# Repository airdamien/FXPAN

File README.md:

# FXPAN

Two Nikon D800 bodies behind one Nikkor-W 180 mm f/5.6. A 50 × 75 mm
beamsplitter sends each body half of the field. The stitch is

**64.80 × 23.9 mm · 2.711:1 · 13248 × 4912 · 65.1 MP**

XPan is 65 × 24 mm at 2.708:1. It is shot from f/5.6 to f/22. The
Nikkor-W covers the stitch wide open. The 44 mm mouths fully clear the
extreme corners from f/8.4; at f/5.6 those corners still pass most of the
light, and the long axis stays clean. The iPhone is the viewfinder and the
stitcher, and it can release both bodies over USB. A Pi Zero and the trigger
board are optional. They pulse both 10-pin remotes together. A yoke is the
alternate base: the same triangle and the same screws, extended out to a
grip past R and a grip on the far side of the plate. The right grip has a
trigger on its front edge.

Buy list, print list, and assembly: [bom.md](bom.md).
The model, the measured focus numbers, and the long alignment notes:
[openscad/fxpan/README.md](openscad/fxpan/README.md).

## On the phone

Landscape on an iPhone 17 Pro Max, in simulate mode.

Partly folded on an iPhone Duo. The picture and the last shots stay above the hinge. The controls and the shutter sit below it.

## Panoramic video

Drive chooses Still or Video. Video records both D800s, copies both clips
to the phone, lines the frames up, and stitches a panorama movie. The
shutter starts the recording and stops it. Each body writes a MOV on its
card, and that copy stays.

Both bodies are set up together. The record command then goes to both at
once, and the stop does the same. The phone keeps the few milliseconds
between the two starts, matches how the picture moves in each clip, and
drops the leading frames from the body that started first. Stitch again
runs that match and the stitch a second time.

Exposure is manual and shared: ISO, shutter, and aperture. Aperture is
written with live view down, which is when a D800 will take it. The bodies
are back on stills before the next frame.

One pair of frames sets the overlap, the warp, the crop, and the tone.
Every later frame uses that fit, with a multiband blend. A weak overlap
fit uses the rig's feather for the whole clip.

Playback plays the panorama, and each body's clip on its own. Share,
protect, delete, and Stitch again are there.

## A Canon, as a try

System has a Canon switch. It stays off until you turn it on. One body, not the pair, and not the stitch.

The camera's USB connection is photo import / remote control. Live view, the shutter, and the copy use that body. The JPEG shows in the roll. A CR3 is saved beside it. The file stays on the card. Turn the switch off and the Nikon pair is back.

## How it goes together

The plate is in the tray, coating toward the lens, 75 mm across the fold.
The two arms leave the box at a right angle. The base carries both bodies.
The mouths are printed F. The lens is the Nikkor-W.

The board is optional. USB release fires both bodies and brings the frames back. The board is the 10-pin path: blue is focus, red is shutter, one pair for each body.

## What the two frames become

## The ray trace

The plate is 75 mm across the fold. At 45° that presents 53 mm, against the
44 mm the stitch needs at f/5.6.

A 2× anamorphic on the front of the 180 is drawn, not fitted on this rig.
Spherical is 20.3° at 50 m. 1.5× is 30.1°. 2× is 39.5°.

```
python kraken/fxpan_paths.py    # exits non-zero if the body and the numbers disagree
python kraken/fxpan_scene.py    # the countryside above
```

## Where the rest went

The D7000 hybrid, the V, the shifted kits, the 5D and α7 forks, and their
export scripts are in [archive/](archive/EARLIER.md). They are not this camera.

## Credits

The D800s in the assembly pictures are mariusimv's approximate model,
[Thingiverse #4815092](https://www.thingiverse.com/thing:4815092).

The printed F mouths start from Archive-663's Nikon mount,
[CC BY-NC-SA 4.0](https://github.com/Archive-663/lensMounts).

The metric threads are Ryan A. Colyer's `threads.scad`,
[CC0](https://www.thingiverse.com/thing:1686322).

The earlier D7000 ghost and the stand-in lens barrel are José Pedro's
Nikon DSLR,
[Printables #1733741](https://www.printables.com/model/1733741-nikon-dslr-camera-model-3d-printable),
CC BY-NC-SA 4.0.

The monitor case is Wormfingers' HAMTYSAN 10.1 enclosure,
[Printables #1041827](https://www.printables.com/model/1041827-hamtysan-101-touchscreen-enclosure),
CC BY 4.0.

The Pi 4 in those older pictures is a Printables mesh, lined up to
[Raspberry Pi's mechanical drawing](https://datasheets.raspberrypi.com/rpi4/raspberry-pi-4-mechanical-drawing.pdf).

The countryside in the anamorphic figure is
[Radek Hloch, CC BY-SA 4.0](https://commons.wikimedia.org/wiki/File:Landscape_of_Tuscany_3.jpg).

The app is set in Jost, SIL Open Font License 1.1,
[The Jost Project Authors](https://github.com/indestructible-type/Jost).

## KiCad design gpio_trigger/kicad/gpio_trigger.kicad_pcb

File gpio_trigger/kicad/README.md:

# KiCad project

1. Open `gpio_trigger.kicad_pro` in KiCad 9.
2. Schematic and PCB are generated by `python3 ../gen_cad.py` — parts placed, traces routed, bottom GND pour filled.
3. Both 3.5 mm jacks are on the pin-1 end of the header (away from the Pi Ethernet jack). Solder the 2×20 socket on the bottom.
4. Fabrication zip: `../fab/pcbway/gpio_trigger-pcbway.zip`.

Reference drawings: `../schematic.svg`, `../layout-pcb.svg`, `../layout-perf.svg`.

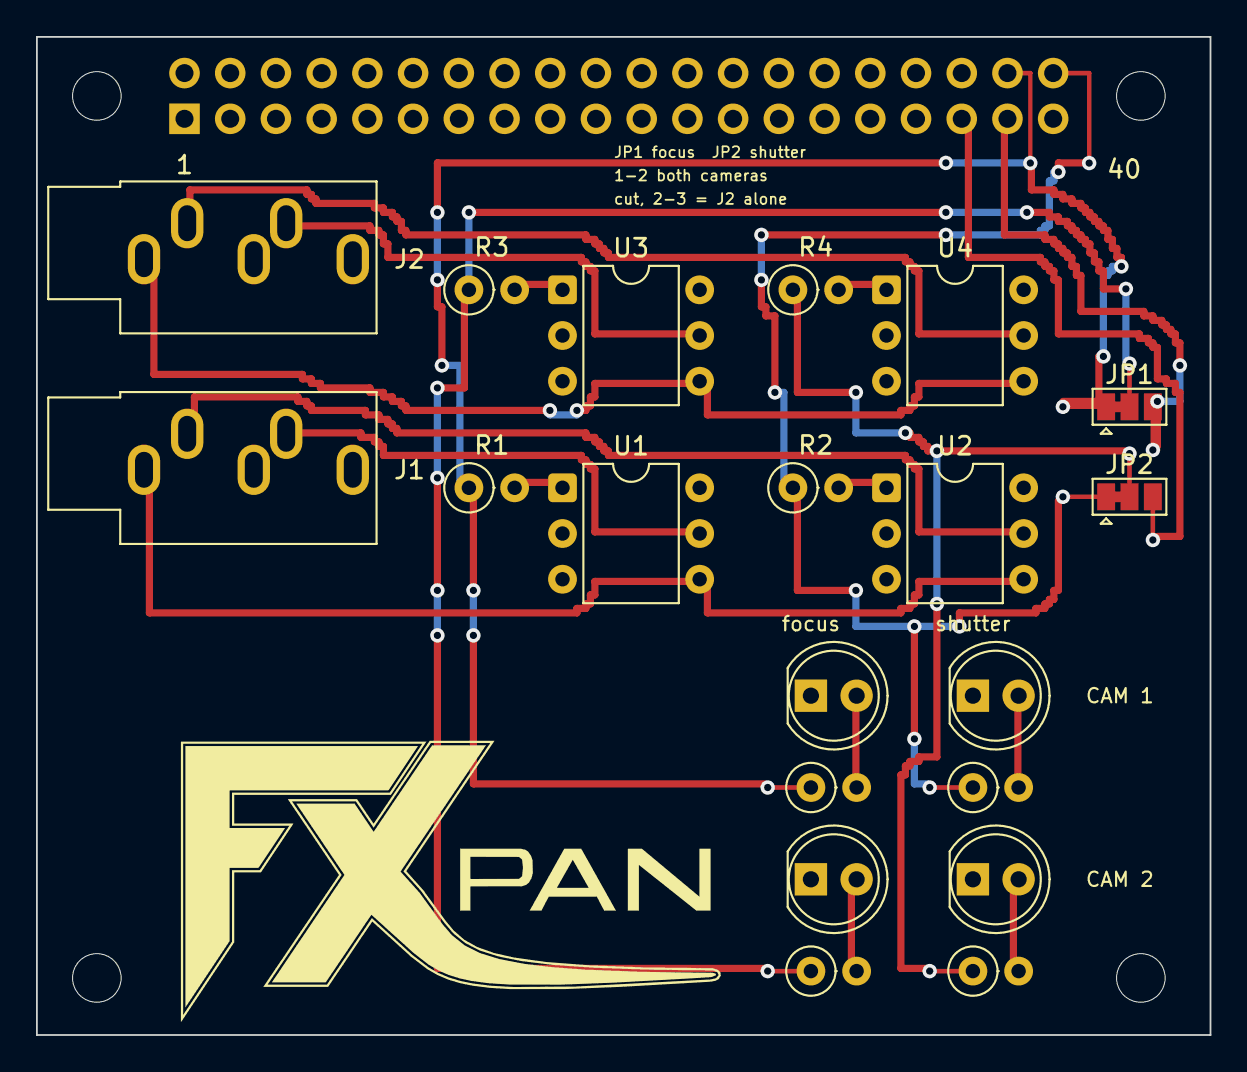
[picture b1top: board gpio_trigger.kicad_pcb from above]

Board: 2 copper layers, 65.2 x 55.5 mm, 25 parts (1 on the bottom side), 21 nets.

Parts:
D1: 1 focus; LED_D5.0mm
D2: 1 shutter; LED_D5.0mm
D3: 2 focus; LED_D5.0mm
D4: 2 shutter; LED_D5.0mm
H1, H2, H3, H4: M2.5; MountingHole_2.7mm_M2.5
J1: TRS_CAM_A; Jack_3.5mm_CUI_SJ1-3535NG_Horizontal
J2: TRS_CAM_B; Jack_3.5mm_CUI_SJ1-3535NG_Horizontal
J3: Pi_GPIO; PinSocket_2x20_P2.54mm_Vertical
JP1: J2_focus; SolderJumper-3_P1.3mm_Bridged12_Pad1.0x1.5mm
JP2: J2_shutter; SolderJumper-3_P1.3mm_Bridged12_Pad1.0x1.5mm
R1, R2, R3, R4, R5, R6, R7, R8: 330; R_Axial_DIN0207_L6.3mm_D2.5mm_P2.54mm_Vertical
U1, U2, U3, U4: 4N35; DIP-6_W7.62mm

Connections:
B_FOCUS: J3.37, JP1.3
B_SHUTTER: J3.35, JP2.3
D1_A: D1.2, R5.2
D2_A: D2.2, R6.2
D3_A: D3.2, R7.2
D4_A: D4.2, R8.2
FOCUS: J3.38, JP1.1, R1.1, R5.1
GND: D1.1, D2.1, D3.1, D4.1, J3.6, J3.9, J3.14, J3.20, J3.25, J3.30, J3.34, J3.39, U1.2, U2.2, U3.2, U4.2
J1_RING: J1.R, U1.5
J1_SLEEVE: J1.S, U1.4, U2.4
J1_TIP: J1.T, U2.5
J2_FOCUS: JP1.2, R3.1, R7.1
J2_RING: J2.R, U3.5
J2_SHUTTER: JP2.2, R4.1, R8.1
J2_SLEEVE: J2.S, U3.4, U4.4
J2_TIP: J2.T, U4.5
R1_LED: R1.2, U1.1
R2_LED: R2.2, U2.1
R3_LED: R3.2, U3.1
R4_LED: R4.2, U4.1
SHUTTER: J3.40, JP2.1, R2.1, R6.1

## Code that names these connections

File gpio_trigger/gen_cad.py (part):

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  <!-- Pi -->
  <rect x="40" y="90" width="170" height="150" class="pi" rx="8"/>
  <text x="58" y="118" class="lbl" font-weight="bold">Raspberry Pi GPIO</text>
  <text x="58" y="142" class="lbl">BCM 20 (pin 38) — FOCUS</text>
  <text x="58" y="166" class="lbl">BCM 21 (pin 40) — SHUTTER</text>
  <text x="58" y="190" class="lbl">GND (pin 39) · J2 alt: pin 37 focus, pin 35 shutter</text>
  <text x="58" y="220" class="sub">3.3 V logic · no battery</text>

  <!-- isolation barrier -->
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    ]

    def opto_block(x: int, y: int, name: str, rname: str, jack: str, role: str, contact: str) -> str:
        gpio_y = 138 if role == "focus" else 162
        parts = [
            f'  <line x1="300" y1="{gpio_y}" x2="{x}" y2="{gpio_y}" class="bus"/>',
            f'  <rect x="{x}" y="{y}" width="28" height="14" fill="#fff" stroke="#333"/>',
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  <text x="58" y="612" class="lbl">1. FOCUS high → ring→sleeve on both jacks</text>
  <text x="58" y="634" class="lbl">2. wait 50–200 ms</text>
  <text x="58" y="656" class="lbl">3. SHUTTER high → tip→sleeve · pulse · release shutter · release focus</text>
  <text x="560" y="612" class="sub">Nikon 10-pin: pin 9 focus, pin 4 shutter, pin 6 ground</text>
  <text x="560" y="634" class="sub">If tip/ring swapped on cable, swap GPIO 20/21 at Pi only</text>
"""
    path.write_text(svg + "\n".join(body) + jacks + "\n</svg>\n")
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    leg_y = 480
    lines += [
        f'<text x="30" y="{leg_y}" font-weight="bold">Wire routing (see netlist.csv)</text>',
        f'<line x1="30" y1="{leg_y+20}" x2="80" y2="{leg_y+20}" class="wire-f"/><text x="88" y="{leg_y+24}">FOCUS (GPIO 20)</text>',
        f'<line x1="30" y1="{leg_y+40}" x2="80" y2="{leg_y+40}" class="wire-s"/><text x="88" y="{leg_y+44}">SHUTTER (GPIO 21)</text>',
        f'<line x1="30" y1="{leg_y+60}" x2="80" y2="{leg_y+60}" class="wire-g"/><text x="88" y="{leg_y+64}">GND (LED cathodes only)</text>',
        f'<text x="30" y="{leg_y+95}" fill="#555">Drill 6 mm panel holes for jacks on short wall · keep camera-side leads short</text>',
        "</svg>",
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def write_netlist(path: Path) -> None:
    rows = [
        "net,from,to",
        "FOCUS,GPIO20,R1.1",
        "FOCUS,GPIO20,JP1.1",
        "J2_FOCUS,JP1.2,R3.1",
        "B_FOCUS,JP1.3,GPIO26",
        "FOCUS,R1.2,U1.1",
        "J2_FOCUS,R3.2,U3.1",
        "SHUTTER,GPIO21,R2.1",
        "SHUTTER,GPIO21,JP2.1",
        "J2_SHUTTER,JP2.2,R4.1",
        "B_SHUTTER,JP2.3,GPIO19",
        "SHUTTER,R2.2,U2.1",
        "J2_SHUTTER,R4.2,U4.1",
        "GND,GPIO_GND,U1.2",
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        "J1_TIP,U2.5,J1.TIP",
        "J2_RING,U3.5,J2.RING",
        "J2_TIP,U4.5,J2.TIP",
        "FOCUS,GPIO20,R5.1",
        "FOCUS,R5.2,D1.A",
        "GND,D1.K,GPIO_GND",
        "SHUTTER,GPIO21,R6.1",
        "SHUTTER,R6.2,D2.A",
        "GND,D2.K,GPIO_GND",
        "J2_FOCUS,R7.1,D3.A",
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            **sim_off,
        )
    )
    parts.append(_glabel("FOCUS", 40, 220 - 5.08))
    parts.append(_glabel("GND", 40, 220 + 5.08))
    parts.append(
        _sch_symbol(
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            **sim_off,
        )
    )
    parts.append(_glabel("SHUTTER", 40, 245 - 5.08))
    parts.append(_glabel("GND", 40, 245 + 5.08))
    for ref, y, hi, lo in (
        ("RSIM1", 220, "FOCUS", "J2_FOCUS"),
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
JP1 (focus) and JP2 (shutter) ship with pads 1–2 bridged, so both cameras follow pin 38 and pin 40. To drive camera B on its own pins, cut that bridge and solder pad 2 to pad 3. J1 stays on pin 38 / pin 40.

## Perfboard build (alternate)

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## Test

```bash
python3 gpio_seq.py --hold-focus   # meter: ring→sleeve on both jacks
python3 gpio_seq.py                # full sequence
```
"""
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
